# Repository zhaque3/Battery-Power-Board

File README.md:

# Battery Power Board

**Project:** Battery Power Board — power distribution, monitoring, and telemetry board for the University of Alberta EcoCar Prototype Vehicle.

**Vehicle:** 2025 Hydrogen Prototype (Sally). 1st Place, Shell Eco Marathon Hydrogen Prototype Category  
**Competition Year:** 2025

---

## Overview

The Battery Power Board serves as the central power monitoring and distribution interface between the vehicle’s energy sources and downstream subsystems.  

It measures battery and regulated rail voltages and currents, monitors thermal conditions, computes energy usage, and communicates system status over the vehicle CAN bus.

---

## Key Functions

- Monitor battery input voltage and current
- Measure regulated output rails (12 V and 7 V)
- Monitor thermal conditions of critical power components
- Track energy consumption over time
- Display live system data on a local OLED
- Communicate telemetry and fault states over CAN bus
- Respond to vehicle safety events (e.g. hydrogen alarm)

---

## Power Architecture

### Input

- Battery input monitored via voltage divider
- Hall effect current sensing
- Designed for continuous monitoring under dynamic load conditions

### Output Rails

- **12 V Rail**
  - Voltage and current monitored
  - Supplies downstream electronics and subsystems
- **7 V Rail**
  - Voltage and current monitored
  - Intended for low power or auxiliary loads

---

## Sensing & Measurement

### Electrical Measurements

The board continuously measures:

- Battery input voltage
- Battery input current
- 12 V output voltage
- 12 V output current
- 7 V output voltage
- 7 V output current

These measurements allow real time estimation of power flow and system loading.

### Thermal Monitoring

- Multiple analog temperature sensors placed near:
  - Buck regulator
  - Output power stage
  - Control electronics
- Enables detection of abnormal thermal conditions during operation

---

## Energy Tracking

The board integrates measured voltage and current over time to estimate energy usage (joules).  
This data is used for:

- Efficiency analysis
- Post run performance evaluation
- Competition strategy optimization

---

## Local User Interface

- **SSD1306 OLED display**
- Displays:
  - Battery voltage and current
  - Output rail voltages and currents
  - Temperatures of key components
- Automatically switches to an alarm display when a fault condition is received

This allows quick diagnostics during testing without external tools.

---

## CAN Bus Integration

- Fully integrated into the vehicle CAN network
- Transmits:
  - Electrical measurements
  - Thermal data
  - System status flags
- Receives:
  - Safety and fault signals (e.g., hydrogen alarm)
  - Synchronization or status commands from other vehicle modules

The board reacts immediately to safety critical CAN messages by updating system state and user display.

---

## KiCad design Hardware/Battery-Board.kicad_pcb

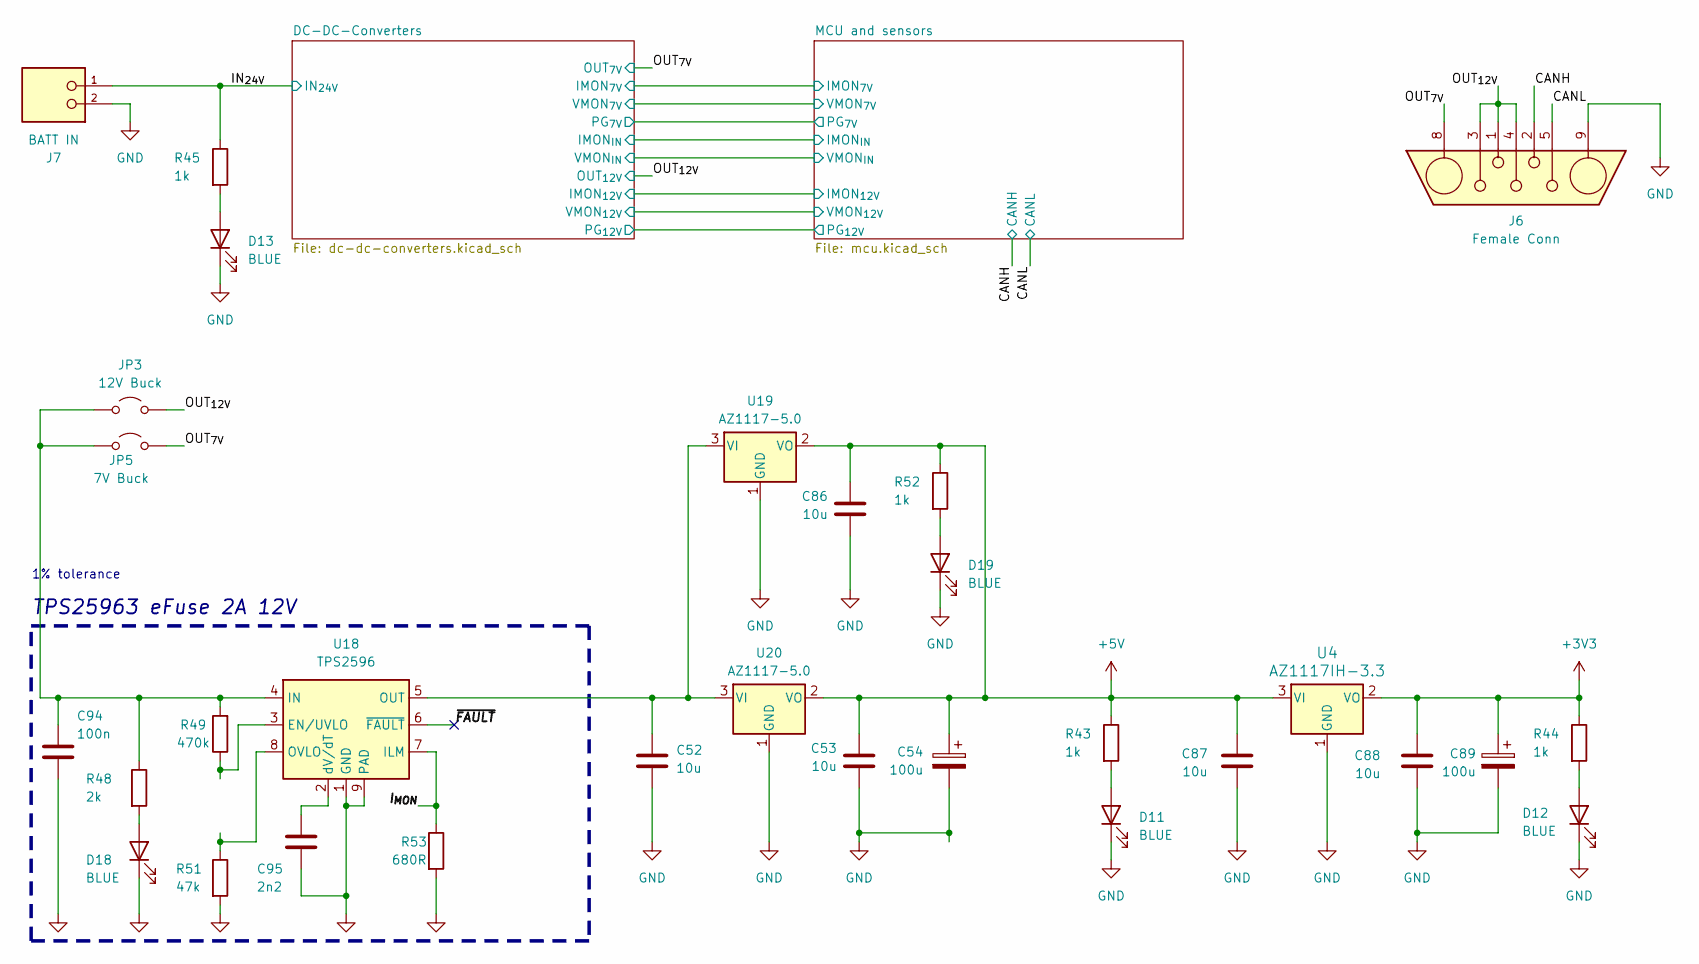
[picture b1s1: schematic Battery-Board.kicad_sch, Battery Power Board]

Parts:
C52, C53, C86, C87, C88: 10u; C_0805_2012Metric; LCSC# C15850
C54, C89: 100u; CP_Elec_6.3x9.9; LCSC# C72478
C94: 100n; C_0603_1608Metric; JLCPCB Part#(Optional) C28233
C95: 2n2; C_0603_1608Metric; JLCPCB Part#(Optional) C1531
D11, D12, D13, D18, D19: BLUE; LED_0603_1608Metric
J6: Female Conn; DB7W2-Female
J7: BATT IN; PHOENIX_1017521; PARTREV 04.01.2018
JP3: 12V Buck; J_0603_Triangular
JP5: 7V Buck; J_0603_Triangular
R43, R44, R45, R52: 1k; R_0603_1608Metric
R48: 2k; R_0603_1608Metric; JLCPCB Part#(Optional) C17604
R49: 470k; R_0603_1608Metric; JLCPCB Part#(optional) C17709
R51: 47k; R_0603_1608Metric; JLCPCB Part#(optional) C17713
R53: 680R; R_0603_1608Metric; JLCPCB Part#(Optional) C23220
U4: AZ1117IH-3.3; SOT-223-3_TabPin2
U18: TPS2596; TI_SO-PowerPAD-8
U19, U20: AZ1117-5.0; SOT-223-3_TabPin2

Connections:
+3V3: C88.1, C89.1, R44.1, U4.2 (VO); also elsewhere on the board
+5V: C53.1, C54.1, C86.1, C87.1, R43.1, R52.1, U4.3 (VI), U19.2 (VO), U20.2 (VO); also elsewhere on the board
/CANH: J6.2; also elsewhere on the board
/CANL: J6.5; also elsewhere on the board
/IN_{24V}: J7.1, R45.1; also elsewhere on the board
/I_{MON}: R53.1, U18.7 (ILM)
/OUT_{7V}: J6.8, JP5.2 (B); also elsewhere on the board
/OUT_{12V}: J6.1, J6.3, J6.4, JP3.2 (B); also elsewhere on the board
/~FAULT: U18.6 (~FAULT)
GND: C52.2, C53.2, C54.2, C86.2, C87.2, C88.2, C89.2, C94.2, C95.2, D11.1 (K), D12.1 (K), D13.1 (K), D18.1 (K), D19.1 (K), J6.9, J7.2, R51.2, R53.2, U4.1 (GND), U18.1 (GND), U18.9 (PAD), U19.1 (GND), U20.1 (GND); also elsewhere on the board
unnamed: D11.2 (A), R43.2
unnamed: D12.2 (A), R44.2
unnamed: D13.2 (A), R45.2
unnamed: D18.2 (A), R48.2
unnamed: D19.2 (A), R52.2
unnamed: C94.1, JP3.1 (A), JP5.1 (A), R48.1, R49.2, U18.4 (IN)
unnamed 90: R49.1, U18.3 (EN/UVLO); also elsewhere on the board
unnamed: C52.1, U18.5 (OUT), U19.3 (VI), U20.3 (VI)
unnamed 92: R51.1, U18.8 (OVLO); also elsewhere on the board
unnamed: C95.1, U18.2 (dV/dT)

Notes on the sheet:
TPS25963 eFuse 2A 12V
1% tolerance

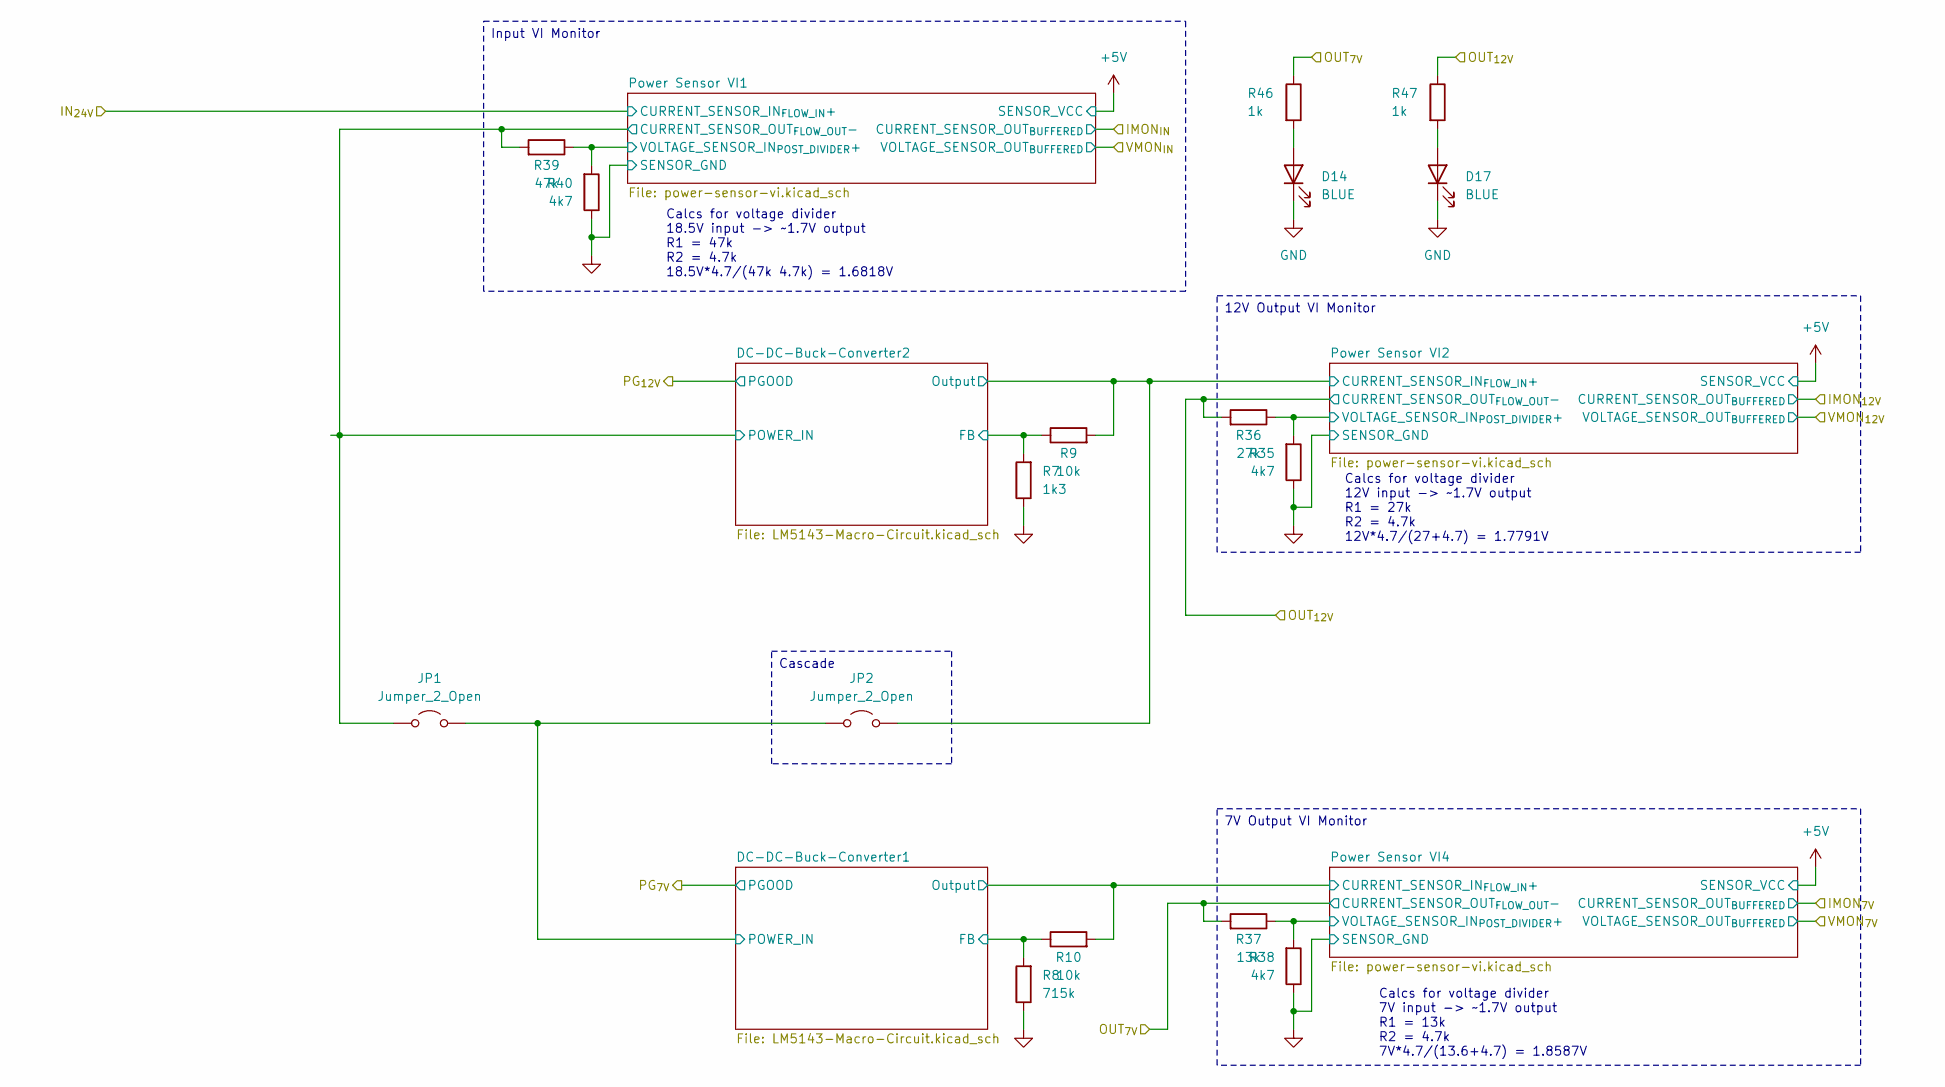
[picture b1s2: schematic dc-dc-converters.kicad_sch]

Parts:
D14, D17: BLUE; LED_0603_1608Metric
JP1, JP2: Jumper_2_Open; Jumper_Micro-Miniature_P5.375mm
R7: 1k3; R_0603_1608Metric
R8: 715k; R_0603_1608Metric
R9, R10: 10k; R_0603_1608Metric
R35, R38, R40: 4k7; R_0603_1608Metric
R36: 27k; R_0603_1608Metric
R37: 13k; R_0603_1608Metric
R39: 47k; R_0603_1608Metric
R46, R47: 1k; R_0603_1608Metric

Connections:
/DC-DC-Converters/DC-DC-Buck-Converter1/FB: R8.2, R10.1; also elsewhere on the board
/DC-DC-Converters/DC-DC-Buck-Converter1/Output: R10.2; also elsewhere on the board
/DC-DC-Converters/DC-DC-Buck-Converter1/POWER_IN: JP1.2 (B), JP2.1 (A); also elsewhere on the board
/DC-DC-Converters/DC-DC-Buck-Converter2/FB: R7.2, R9.1; also elsewhere on the board
/DC-DC-Converters/DC-DC-Buck-Converter2/Output: JP2.2 (B), R9.2; also elsewhere on the board
/DC-DC-Converters/DC-DC-Buck-Converter2/POWER_IN: JP1.1 (A), R39.2; also elsewhere on the board
/DC-DC-Converters/Power Sensor VI1/VOLTAGE_SENSOR_IN_{POST_DIVIDER}+: R39.1, R40.2; also elsewhere on the board
/DC-DC-Converters/Power Sensor VI2/VOLTAGE_SENSOR_IN_{POST_DIVIDER}+: R35.2, R36.1; also elsewhere on the board
/DC-DC-Converters/Power Sensor VI4/VOLTAGE_SENSOR_IN_{POST_DIVIDER}+: R37.1, R38.2; also elsewhere on the board
/OUT_{7V}: R37.2, R46.1; also elsewhere on the board
/OUT_{12V}: R36.2, R47.1; also elsewhere on the board
GND: D14.1 (K), D17.1 (K), R7.1, R8.1, R35.1, R38.1, R40.1; also elsewhere on the board
unnamed: D14.2 (A), R46.2
unnamed: D17.2 (A), R47.2

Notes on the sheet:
Calcs for voltage divider 18.5V input -> ~1.7V output R1 = 47k R2 = 4.7k 18.5V*4.7/(47k 4.7k) = 1.6818V
Calcs for voltage divider 7V input -> ~1.7V output R1 = 13k R2 = 4.7k 7V*4.7/(13.6+4.7) = 1.8587V
Calcs for voltage divider 12V input -> ~1.7V output R1 = 27k R2 = 4.7k 12V*4.7/(27+4.7) = 1.7791V
12V Output VI Monitor
7V Output VI Monitor
Input VI Monitor
Cascade

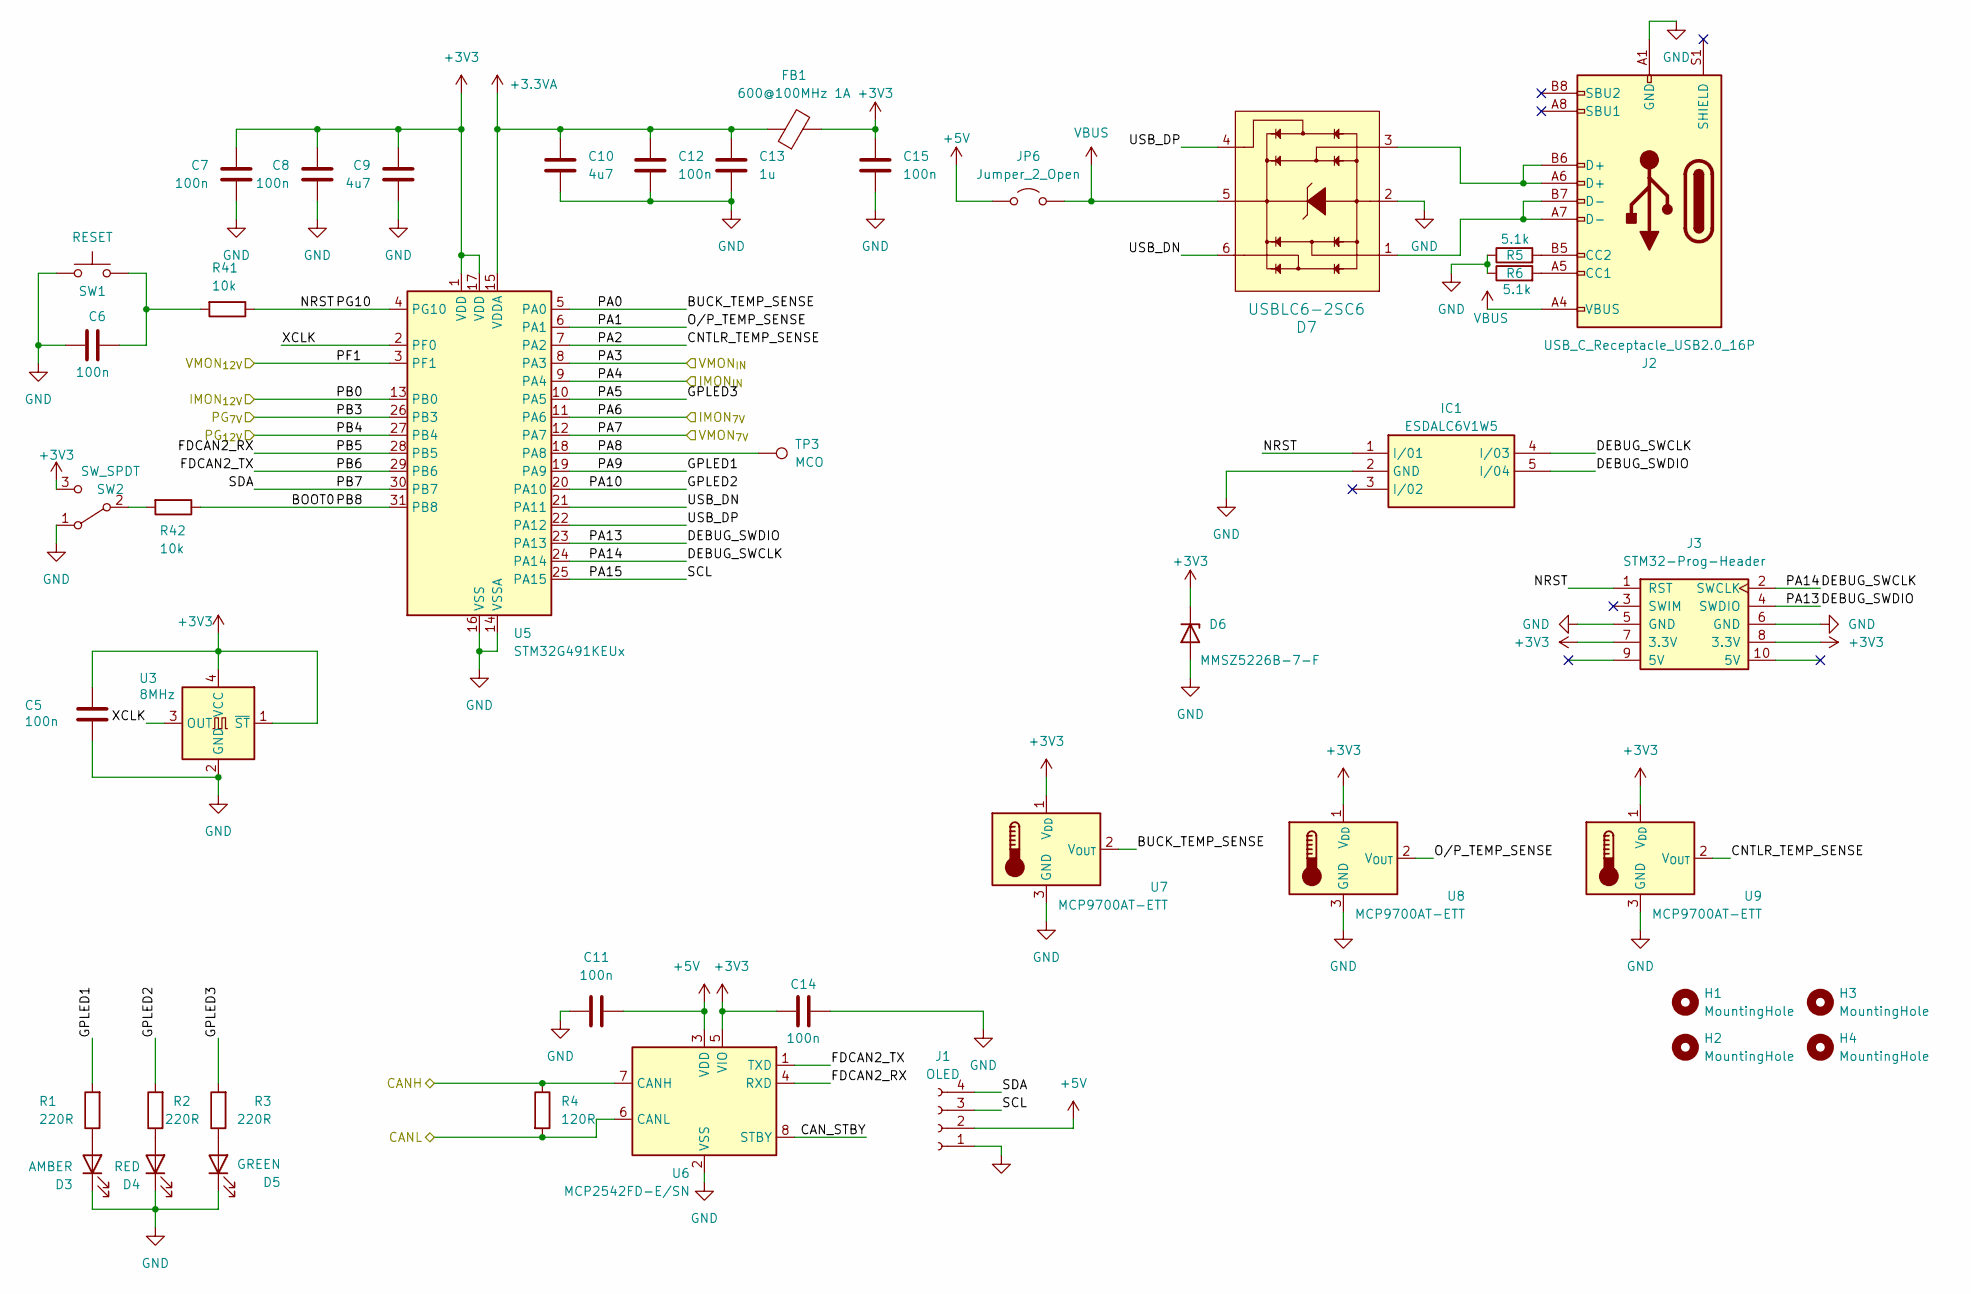
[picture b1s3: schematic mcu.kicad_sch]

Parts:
C5, C6, C11, C14: 100n; C_0603_1608Metric; JLCPCB Part#(Optional) C1525
C7, C8: 100n; C_0603_1608Metric
C9: 4u7; C_0805_2012Metric
C10: 4u7; C_0603_1608Metric; JLCPCB Part#(Optional) C96446
C12: 100n; C_0603_1608Metric; JLCPCB Part#(Optional) C96446
C13: 1u; C_0603_1608Metric; JLCPCB Part#(Optional) C28323
C15: 100n; C_0603_1608Metric; JLCPCB Part#(Optional) C28323
D3: AMBER; LED_0603_1608Metric; JLCPCB Part#(Optional) C2296
D4: RED; LED_0603_1608Metric; JLCPCB Part#(Optional) C84256
D5: GREEN; LED_0603_1608Metric; JLCPCB Part#(Optional) C2297
D6: MMSZ5226B-7-F; D_SOD-123; Digikey # MMSZ5226B-FDICT-ND
D7: USBLC6-2SC6; TSOT-23-6; Digikey # 497-5235-1-ND
FB1: 600@100MHz 1A; L_0603_1608Metric; Digikey # 1934-1474-1-ND
H1, H2, H3, H4: MountingHole; MountingHole_3.5mm
IC1: ESDALC6V1W5; SOT65P210X110-5N; JLCPCB Part#(Optional) C2827626
J1: OLED; Display_128x64_096_I2C
J2: USB_C_Receptacle_USB2.0_16P; USB_C_Receptacle_GCT_USB4105-xx-A_16P_TopMnt_Horizontal
J3: STM32-Prog-Header; PinHeader_2x05_P2.54mm_Vertical
JP6: Jumper_2_Open
R1, R2, R3: 220R; R_0603_1608Metric; JLCPCB Part#(Optional) C17557
R4: 120R; R_0603_1608Metric
R5, R6: 5.1k; R_0603_1608Metric; JLCPCB Part#(Optional) C17557
R41, R42: 10k; R_0603_1608Metric; JLCPCB Part#(Optional) C17557
SW1: RESET; SW_PUSH_6mm_H5mm
SW2: SW_SPDT; SW_SPDT_PCM12; Digikey # 2223-SLW-66527511-SMT-TRCT-ND
TP3: MCO; PinHeader_1x01_P2.54mm_Vertical
U3: 8MHz; Crystal_SMD_3225-4Pin_3.2x2.5mm; Digikey # 535-ASE-8.000MHZ-L-C-TCT-ND
U5: STM32G491KEUx; QFN-32-1EP_5x5mm_P0.5mm_EP3.45x3.45mm
U6: MCP2542FD-E/SN; SOIC-8_3.9x4.9mm_P1.27mm; Digikey # MCP2542FD-E/SN-ND
U7, U8, U9: MCP9700AT-ETT; SOT-23; LCSC# C42288

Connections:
+3.3VA: C10.1, C12.1, C13.1, FB1.1, U5.15 (VDDA)
+3V3: C5.2, C7.1, C8.1, C9.1, C14.2, C15.1, D6.1 (K), FB1.2, J3.7 (3.3V), J3.8 (3.3V), SW2.3 (C), U3.1 (~ST), U3.4 (VCC), U5.1 (VDD), U5.17 (VDD), U6.5 (VIO), U7.1 (V_{DD}), U8.1 (V_{DD}), U9.1 (V_{DD}); also elsewhere on the board
+5V: C11.2, J1.2, JP6.1 (A), U6.3 (VDD); also elsewhere on the board
/CANH: R4.1, U6.7 (CANH); also elsewhere on the board
/CANL: R4.2, U6.6 (CANL); also elsewhere on the board
/MCU and sensors/BUCK_TEMP_SENSE: U5.5 (PA0), U7.2 (V_{OUT})
/MCU and sensors/CAN_STBY: U6.8 (STBY)
/MCU and sensors/CNTLR_TEMP_SENSE: U5.7 (PA2), U9.2 (V_{OUT})
/MCU and sensors/DEBUG_SWCLK: IC1.4 (I/03), J3.2 (SWCLK), U5.24 (PA14)
/MCU and sensors/DEBUG_SWDIO: IC1.5 (I/04), J3.4 (SWDIO), U5.23 (PA13)
/MCU and sensors/FDCAN2_RX: U5.28 (PB5), U6.4 (RXD)
/MCU and sensors/FDCAN2_TX: U5.29 (PB6), U6.1 (TXD)
/MCU and sensors/GPLED1: R1.2, U5.19 (PA9)
/MCU and sensors/GPLED2: R2.2, U5.20 (PA10)
/MCU and sensors/GPLED3: R3.2, U5.10 (PA5)
/MCU and sensors/NRST: IC1.1 (I/01), J3.1 (RST), R41.1, U5.4 (PG10)
/MCU and sensors/O/P_TEMP_SENSE: U5.6 (PA1), U8.2 (V_{OUT})
/MCU and sensors/PA3: U5.8 (PA3); also elsewhere on the board
/MCU and sensors/PA4: U5.9 (PA4); also elsewhere on the board
/MCU and sensors/PA6: U5.11 (PA6); also elsewhere on the board
/MCU and sensors/PA7: U5.12 (PA7); also elsewhere on the board
/MCU and sensors/PA8: TP3.1, U5.18 (PA8)
/MCU and sensors/PA15: J1.3, U5.25 (PA15)
/MCU and sensors/PB0: U5.13 (PB0); also elsewhere on the board
/MCU and sensors/PB3: U5.26 (PB3); also elsewhere on the board
/MCU and sensors/PB4: U5.27 (PB4); also elsewhere on the board
/MCU and sensors/PB7: J1.4, U5.30 (PB7)
/MCU and sensors/PF1: U5.3 (PF1); also elsewhere on the board
/MCU and sensors/USB_DN: D7.6, U5.21 (PA11)
/MCU and sensors/USB_DP: D7.4, U5.22 (PA12)
/MCU and sensors/XCLK: U3.3 (OUT), U5.2 (PF0)
GND: C5.1, C6.1, C7.2, C8.2, C9.2, C10.2, C11.1, C12.2, C13.2, C14.1, C15.2, D3.1 (K), D4.1 (K), D5.1 (K), D6.2 (A), D7.2, IC1.2 (GND), J1.1, J2.A1 (GND), J2.A12 (GND), J2.B1 (GND), J2.B12 (GND), J3.5 (GND), J3.6 (GND), R5.1, R6.1, SW1.1, SW2.1 (A), U3.2 (GND), U5.14 (VSSA), U5.16 (VSS), U5.32 (VSS), U5.33 (VSS), U6.2 (VSS), U6.9 (VSS), U7.3 (GND), U8.3 (GND), U9.3 (GND); also elsewhere on the board
unnamed: C6.2, R41.2, SW1.2
unnamed: D3.2 (A), R1.1
unnamed: D4.2 (A), R2.1
unnamed: D5.2 (A), R3.1
unnamed: D7.1, J2.A7 (D-), J2.B7 (D-)
unnamed: D7.3, J2.A6 (D+), J2.B6 (D+)
unnamed: J2.A5 (CC1), R6.2
unnamed: J2.B5 (CC2), R5.2
unnamed: R42.2, SW2.2 (B)
unnamed: R42.1, U5.31 (PB8)
VBUS: D7.5, J2.A4 (VBUS), J2.A9 (VBUS), J2.B4 (VBUS), J2.B9 (VBUS), JP6.2 (B)

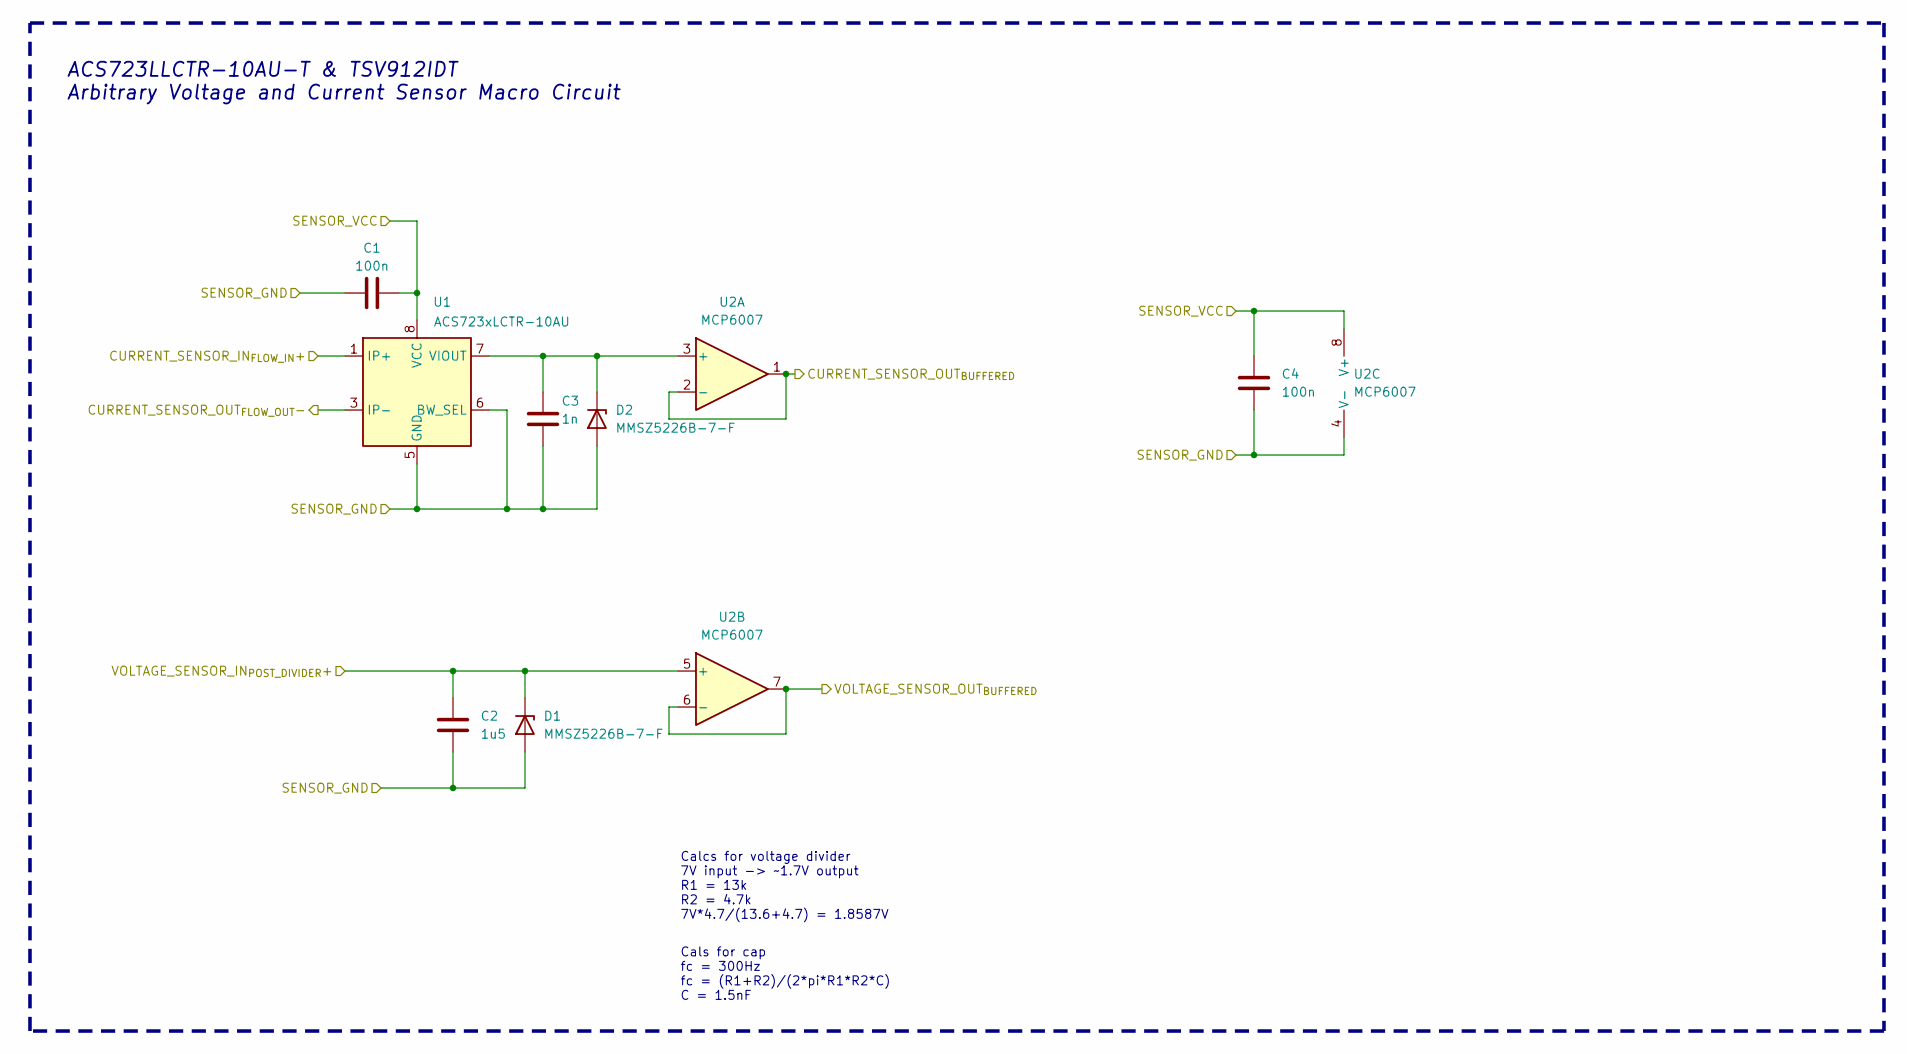
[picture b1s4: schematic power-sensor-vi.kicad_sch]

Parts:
C1, C4: 100n; C_0603_1608Metric; Digikey # CC0603KRX7R7BB104
C2: 1u5; C_0603_1608Metric; JLCPCB Part#(Optional) C28323
C3: 1n; C_0603_1608Metric; JLCPCB Part#(Optional) C1523
D1, D2: MMSZ5226B-7-F; D_SOD-123; Digikey # MMSZ5226B-FDICT-ND
U1: ACS723xLCTR-10AU; SOIC-8_3.9x4.9mm_P1.27mm
U2: MCP6007; SOIC-8_3.9x4.9mm_P1.27mm

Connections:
+5V: C1.1, C4.1, U1.8 (VCC), U2.8 (V+); also elsewhere on the board
/DC-DC-Converters/DC-DC-Buck-Converter2/POWER_IN: U1.3 (IP-), U1.4 (IP-); also elsewhere on the board
/DC-DC-Converters/Power Sensor VI1/VOLTAGE_SENSOR_IN_{POST_DIVIDER}+: C2.1, D1.1 (K), U2.5 (+); also elsewhere on the board
/IN_{24V}: U1.1 (IP+), U1.2 (IP+); also elsewhere on the board
/MCU and sensors/PA3: U2.6 (-), U2.7; also elsewhere on the board
/MCU and sensors/PA4: U2.1, U2.2 (-); also elsewhere on the board
GND: C1.2, C2.2, C3.2, C4.2, D1.2 (A), D2.2 (A), U1.5 (GND), U1.6 (BW_SEL), U2.4 (V-); also elsewhere on the board
unnamed: C3.1, D2.1 (K), U1.7 (VIOUT), U2.3 (+)

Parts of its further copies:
C16, C19, C90, C93: 100n; C_0603_1608Metric; Digikey # CC0603KRX7R7BB104
C17, C91: 1u5; C_0603_1608Metric; JLCPCB Part#(Optional) C28323
C18, C92: 1n; C_0603_1608Metric; JLCPCB Part#(Optional) C1523
D9, D10, D15, D16: MMSZ5226B-7-F; D_SOD-123; Digikey # MMSZ5226B-FDICT-ND
U10, U28: ACS723xLCTR-10AU; SOIC-8_3.9x4.9mm_P1.27mm
U11, U29: MCP6007; SOIC-8_3.9x4.9mm_P1.27mm

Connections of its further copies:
+5V: C16.1, C19.1, C90.1, C93.1, U10.8 (VCC), U11.8 (V+), U28.8 (VCC), U29.8 (V+); also elsewhere on the board
/DC-DC-Converters/DC-DC-Buck-Converter1/Output: U28.1 (IP+), U28.2 (IP+); also elsewhere on the board
/DC-DC-Converters/DC-DC-Buck-Converter2/Output: U10.1 (IP+), U10.2 (IP+); also elsewhere on the board
/DC-DC-Converters/Power Sensor VI2/VOLTAGE_SENSOR_IN_{POST_DIVIDER}+: C17.1, D9.1 (K), U11.5 (+); also elsewhere on the board
/DC-DC-Converters/Power Sensor VI4/VOLTAGE_SENSOR_IN_{POST_DIVIDER}+: C91.1, D15.1 (K), U29.5 (+); also elsewhere on the board
/MCU and sensors/PA6: U29.1, U29.2 (-); also elsewhere on the board
/MCU and sensors/PA7: U29.6 (-), U29.7; also elsewhere on the board
/MCU and sensors/PB0: U11.1, U11.2 (-); also elsewhere on the board
/MCU and sensors/PF1: U11.6 (-), U11.7; also elsewhere on the board
/OUT_{7V}: U28.3 (IP-), U28.4 (IP-); also elsewhere on the board
/OUT_{12V}: U10.3 (IP-), U10.4 (IP-); also elsewhere on the board
GND: C16.2, C17.2, C18.2, C19.2, C90.2, C91.2, C92.2, C93.2, D9.2 (A), D10.2 (A), D15.2 (A), D16.2 (A), U10.5 (GND), U10.6 (BW_SEL), U11.4 (V-), U28.5 (GND), U28.6 (BW_SEL), U29.4 (V-); also elsewhere on the board
unnamed: C18.1, D10.1 (K), U10.7 (VIOUT), U11.3 (+)
unnamed: C92.1, D16.1 (K), U28.7 (VIOUT), U29.3 (+)

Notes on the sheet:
ACS723LLCTR-10AU-T & TSV912IDT Arbitrary Voltage and Current Sensor Macro Circuit
Cals for cap fc = 300Hz fc = (R1+R2)/(2*pi*R1*R2*C) C = 1.5nF
Calcs for voltage divider 7V input -> ~1.7V output R1 = 13k R2 = 4.7k 7V*4.7/(13.6+4.7) = 1.8587V

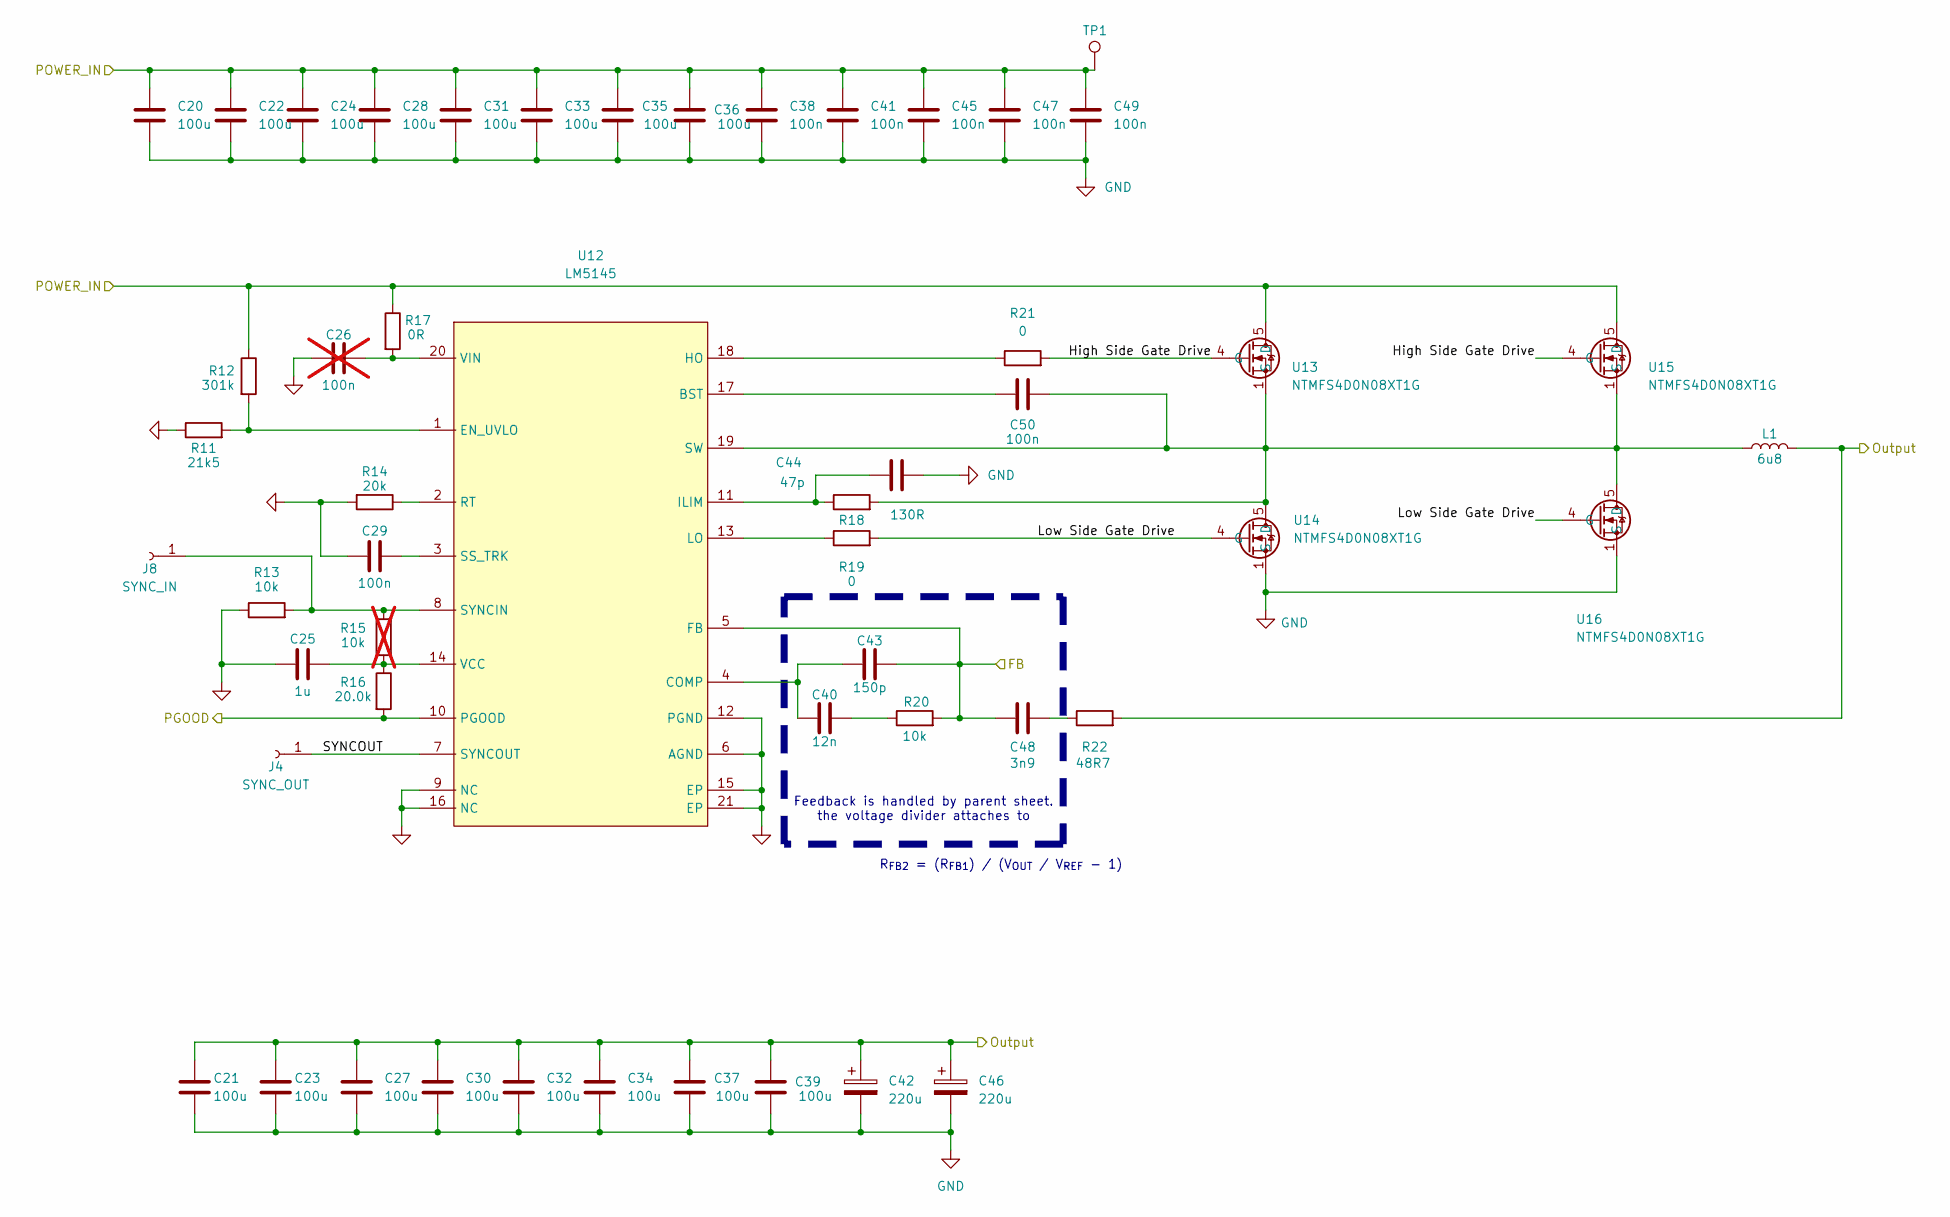
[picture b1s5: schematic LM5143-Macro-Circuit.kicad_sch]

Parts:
C20, C21, C22, C23, C24, C27, C28, C30, C31, C32, C33, C34, C35, C36, C37, C39: 100u; C_1210_3225Metric
C25: 1u; C_0603_1608Metric
C26: 100n; C_0603_1608Metric; not fitted
C29, C38, C41, C45, C47, C49, C50: 100n; C_0603_1608Metric
C40: 12n; C_0603_1608Metric
C42, C46: 220u; CAP_EEE1HA221P
C43: 150p; C_0603_1608Metric
C44: 47p; C_0603_1608Metric
C48: 3n9; C_0603_1608Metric
J4: SYNC_OUT; PinHeader_1x01_P2.54mm_Vertical
J8: SYNC_IN; PinHeader_1x01_P2.54mm_Vertical
L1: 6u8; L_Bourns_SRR1208_12.7x12.7mm
R11: 21k5; R_0603_1608Metric
R12: 301k; R_0603_1608Metric
R13, R20: 10k; R_0603_1608Metric
R14: 20k; R_0603_1608Metric
R15: 10k; R_0603_1608Metric; not fitted
R16: 20.0k; R_0603_1608Metric
R17: 0R; R_0603_1608Metric
R18: 130R; R_0603_1608Metric
R19, R21: 0; R_0603_1608Metric
R22: 48R7; R_0603_1608Metric
TP1: TestPoint; PinHeader_1x01_P2.54mm_Vertical
U12: LM5145; Texas_RGY_R-PVQFN-N20_EP2.05x3.05mm_ThermalVias
U13, U14, U15, U16: NTMFS4D0N08XT1G; PowerMosDFNHybrid

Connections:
/DC-DC-Converters/DC-DC-Buck-Converter1/FB: C43.2, C48.1, R20.2, U12.5 (FB); also elsewhere on the board
/DC-DC-Converters/DC-DC-Buck-Converter1/High Side Gate Drive: R21.2, U13.4 (G), U15.4 (G)
/DC-DC-Converters/DC-DC-Buck-Converter1/Low Side Gate Drive: R19.2, U14.4 (G), U16.4 (G)
/DC-DC-Converters/DC-DC-Buck-Converter1/Output: C21.1, C23.1, C27.1, C30.1, C32.1, C34.1, C37.1, C39.1, C42.1, C46.1, L1.2, R22.2; also elsewhere on the board
/DC-DC-Converters/DC-DC-Buck-Converter1/POWER_IN: C20.1, C22.1, C24.1, C28.1, C31.1, C33.1, C35.1, C36.1, C38.1, C41.1, C45.1, C47.1, C49.1, R12.1, R17.1, TP1.1, U13.5 (D), U15.5 (D); also elsewhere on the board
/DC-DC-Converters/DC-DC-Buck-Converter1/SYNCOUT: J4.1, U12.7 (SYNCOUT)
/MCU and sensors/PB3: R16.2, U12.10 (PGOOD); also elsewhere on the board
GND: C20.2, C21.2, C22.2, C23.2, C24.2, C25.1, C26.1, C27.2, C28.2, C29.1, C30.2, C31.2, C32.2, C33.2, C34.2, C35.2, C36.2, C37.2, C38.2, C39.2, C41.2, C42.2, C44.1, C45.2, C46.2, C47.2, C49.2, R11.1, R13.1, R14.2, U12.6 (AGND), U12.9 (NC), U12.12 (PGND), U12.15 (EP), U12.16 (NC), U12.21 (EP), U14.1 (S), U14.2 (S), U14.3 (S), U16.1 (S), U16.2 (S), U16.3 (S); also elsewhere on the board
unnamed: C40.2, R20.1
unnamed: C48.2, R22.1
unnamed: J8.1, R13.2, R15.1, U12.8 (SYNCIN)
unnamed: C50.2, U12.17 (BST)
unnamed: C40.1, C43.1, U12.4 (COMP)
unnamed: R11.2, R12.2, U12.1 (EN_UVLO)
unnamed: R21.1, U12.18 (HO)
unnamed: C44.2, R18.1, U12.11 (ILIM)
unnamed: R19.1, U12.13 (LO)
unnamed: R14.1, U12.2 (RT)
unnamed: C29.2, U12.3 (SS_TRK)
unnamed: C50.1, L1.1, R18.2, U12.19 (SW), U13.1 (S), U13.2 (S), U13.3 (S), U14.5 (D), U15.1 (S), U15.2 (S), U15.3 (S), U16.5 (D)
unnamed: C25.2, R15.2, R16.1, U12.14 (VCC)
unnamed: C26.2, R17.2, U12.20 (VIN)

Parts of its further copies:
C55, C56, C57, C58, C59, C62, C63, C65, C66, C67, C68, C69, C70, C71, C72, C74: 100u; C_1210_3225Metric
C60: 1u; C_0603_1608Metric
C61: 100n; C_0603_1608Metric; not fitted
C73, C76, C80, C82, C84, C85: 100n; C_0603_1608Metric
C77, C81: 220u; CAP_EEE1HA221P
J5: SYNC_OUT; PinHeader_1x01_P2.54mm_Vertical
J9: SYNC_IN; PinHeader_1x01_P2.54mm_Vertical
L2: 6u8; L_Bourns_SRR1208_12.7x12.7mm
R25, R32: 10k; R_0603_1608Metric
R27: 10k; R_0603_1608Metric; not fitted
R28: 20.0k; R_0603_1608Metric
R31, R33: 0; R_0603_1608Metric
TP2: TestPoint; PinHeader_1x01_P2.54mm_Vertical
U21: LM5145; Texas_RGY_R-PVQFN-N20_EP2.05x3.05mm_ThermalVias
U22, U23, U24, U25: NTMFS4D0N08XT1G; PowerMosDFNHybrid

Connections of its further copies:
/DC-DC-Converters/DC-DC-Buck-Converter2/FB: R32.2, U21.5 (FB); also elsewhere on the board
/DC-DC-Converters/DC-DC-Buck-Converter2/High Side Gate Drive: R33.2, U22.4 (G), U24.4 (G)
/DC-DC-Converters/DC-DC-Buck-Converter2/Low Side Gate Drive: R31.2, U23.4 (G), U25.4 (G)
/DC-DC-Converters/DC-DC-Buck-Converter2/Output: C56.1, C58.1, C62.1, C65.1, C67.1, C69.1, C72.1, C74.1, C77.1, C81.1, L2.2; also elsewhere on the board
/DC-DC-Converters/DC-DC-Buck-Converter2/POWER_IN: C55.1, C57.1, C59.1, C63.1, C66.1, C68.1, C70.1, C71.1, C73.1, C76.1, C80.1, C82.1, C84.1, TP2.1, U22.5 (D), U24.5 (D); also elsewhere on the board
/DC-DC-Converters/DC-DC-Buck-Converter2/SYNCOUT: J5.1, U21.7 (SYNCOUT)
/MCU and sensors/PB4: R28.2, U21.10 (PGOOD); also elsewhere on the board
GND: C55.2, C56.2, C57.2, C58.2, C59.2, C60.1, C61.1, C62.2, C63.2, C65.2, C66.2, C67.2, C68.2, C69.2, C70.2, C71.2, C72.2, C73.2, C74.2, C76.2, C77.2, C80.2, C81.2, C82.2, C84.2, R25.1, U21.6 (AGND), U21.9 (NC), U21.12 (PGND), U21.15 (EP), U21.16 (NC), U21.21 (EP), U23.1 (S), U23.2 (S), U23.3 (S), U25.1 (S), U25.2 (S), U25.3 (S); also elsewhere on the board
unnamed 55: R32.1; also elsewhere on the board
unnamed: J9.1, R25.2, R27.1, U21.8 (SYNCIN)
unnamed: C85.2, U21.17 (BST)
unnamed 95: U21.4 (COMP); also elsewhere on the board
unnamed 96: U21.1 (EN_UVLO); also elsewhere on the board
unnamed: R33.1, U21.18 (HO)
unnamed 98: U21.11 (ILIM); also elsewhere on the board
unnamed: R31.1, U21.13 (LO)
unnamed 100: U21.2 (RT); also elsewhere on the board
unnamed 101: U21.3 (SS_TRK); also elsewhere on the board
unnamed 102: C85.1, L2.1, U21.19 (SW), U22.1 (S), U22.2 (S), U22.3 (S), U23.5 (D), U24.1 (S), U24.2 (S), U24.3 (S), U25.5 (D); also elsewhere on the board
unnamed: C60.2, R27.2, R28.1, U21.14 (VCC)
unnamed 104: C61.2, U21.20 (VIN); also elsewhere on the board

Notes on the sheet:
Feedback is handled by parent sheet. the voltage divider attaches to
R_{FB2} = (R_{FB1}) / (V_{OUT} / V_{REF} - 1)
